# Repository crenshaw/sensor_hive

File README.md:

# Sensor Hive

Another chapter in the Internet of Things.  Sensing the world and pushing data to the cloud.

## About

Buildings are responsible for up to 40% of energy use.  Students and
faculty at the University of Portland are working towards a low-cost
solution for sensing building lighting systems in order to find ways
to provide more efficient lighting.

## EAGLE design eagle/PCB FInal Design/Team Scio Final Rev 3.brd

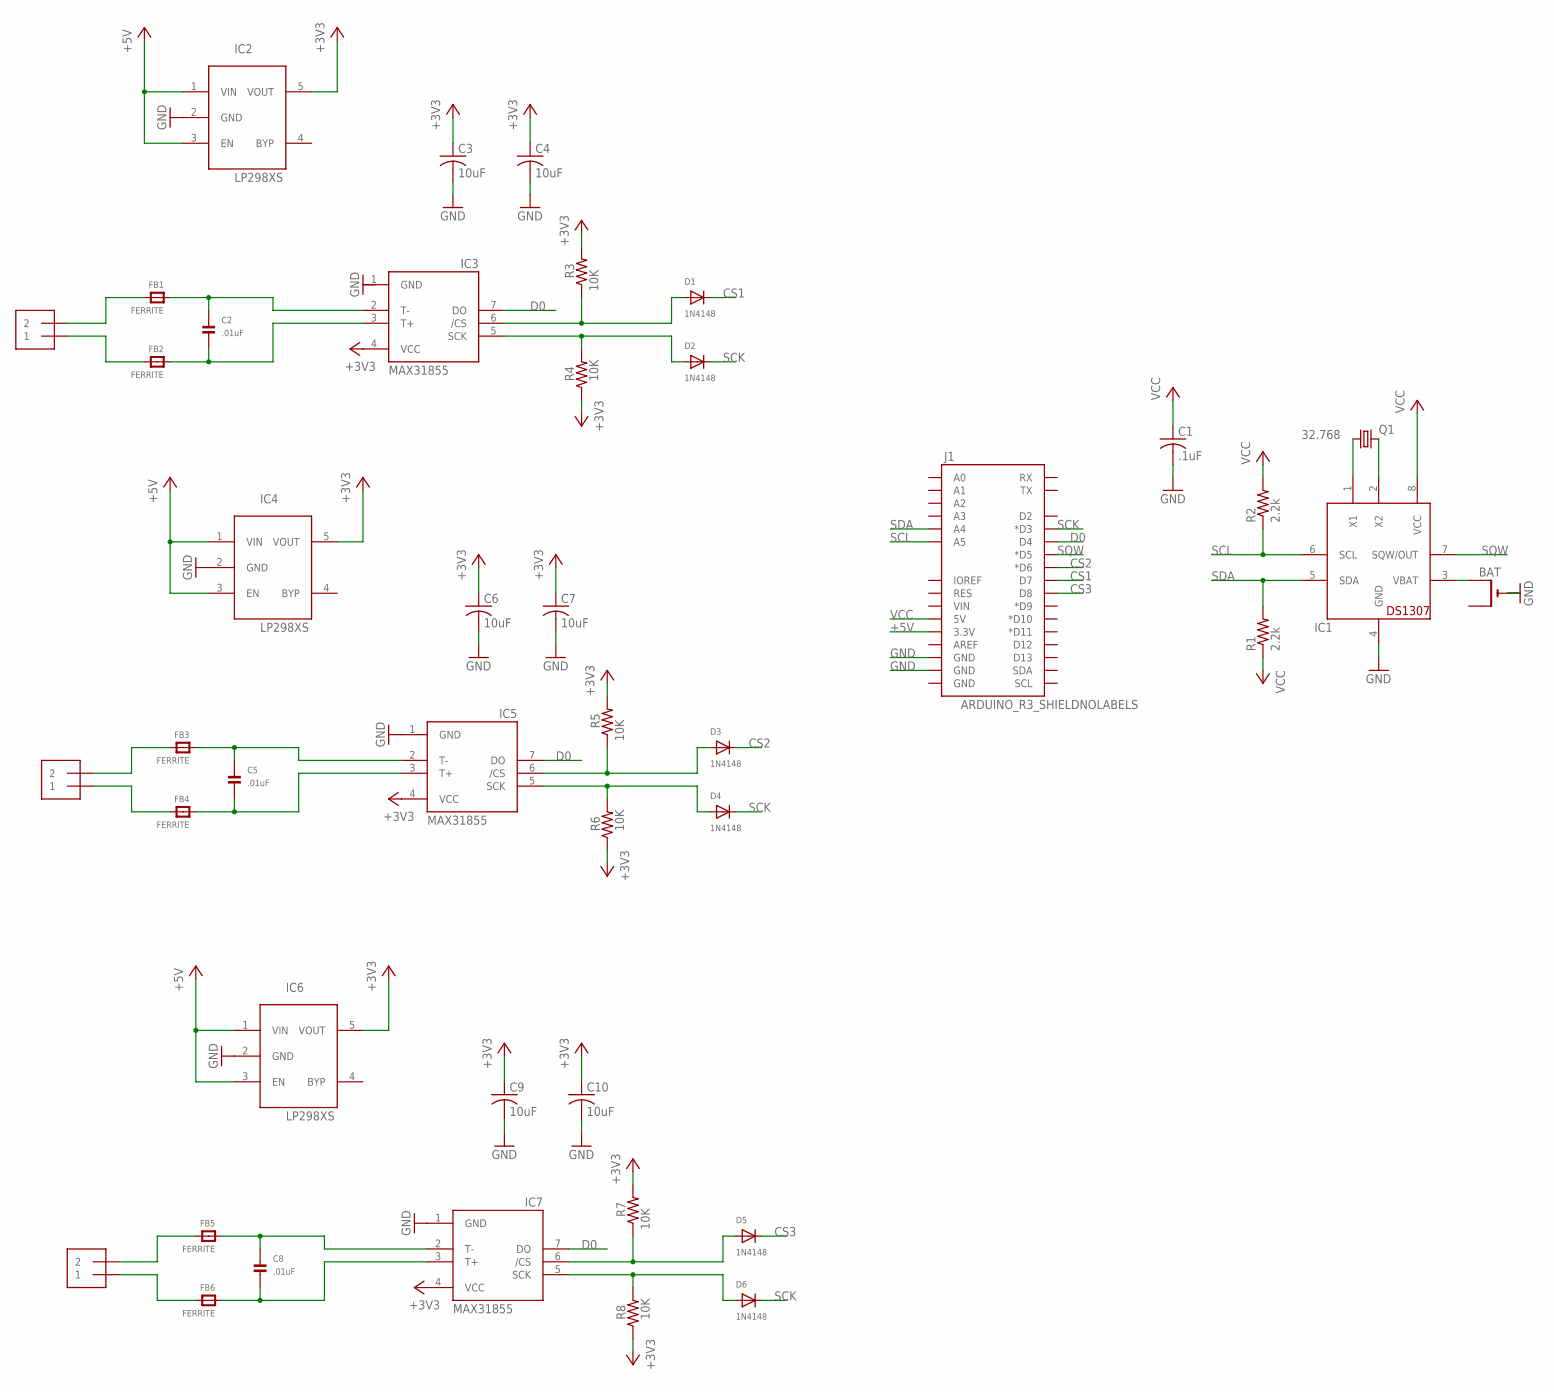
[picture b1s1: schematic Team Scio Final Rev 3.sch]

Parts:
C1: .1uF; C025-025X050
C2, C5, C8: .01uF; 0805
C3, C4, C6, C7, C9, C10: 10uF; C0805K
D1, D2, D3, D4, D5, D6: 1N4148; SOD-323F
FB1, FB2, FB3, FB4, FB5, FB6: FERRITE; 0805
IC1: DS1307; DIL08
IC2, IC4, IC6: LP298XS; SOT23-5L
IC3, IC5, IC7: MAX31855; SO08
J1: ARDUINO_R3_SHIELDNOLABELS; UNO_R3_SHIELD_NOLABELS
J2: J1; 1X2-3.5MM
J3, J4: 1X2-3.5MM
Q1: 32.768; TC38H
R1, R2: 2.2k; M1206
R3, R4, R5, R6, R7, R8: 10K; M1206
RTC: BAT; CR1220-THM

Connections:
+3V3: C3.1, C4.1, C6.1, C7.1, C9.1, C10.1, IC2.5 (VOUT), IC3.4 (VCC), IC4.5 (VOUT), IC5.4 (VCC), IC6.5 (VOUT), IC7.4 (VCC), R3.2, R4.1, R5.2, R6.1, R7.2, R8.1
+5V: IC2.1 (VIN), IC2.3 (EN), IC4.1 (VIN), IC4.3 (EN), IC6.1 (VIN), IC6.3 (EN), J1.3.3V
CS1: D1.C, J1.D7
CS2: D3.C, J1.D6 (*D6)
CS3: D5.C, J1.D8
D0: IC3.7 (DO), IC5.7 (DO), IC7.7 (DO), J1.D4
GND: C1.2, C3.2, C4.2, C6.2, C7.2, C9.2, C10.2, IC1.4 (GND), IC2.2 (GND), IC3.1 (GND), IC4.2 (GND), IC5.1 (GND), IC6.2 (GND), IC7.1 (GND), J1.GND@1 (GND), J1.GND@2 (GND), RTC.-
unnamed: IC1.3 (VBAT), RTC.+2 (+1)
unnamed: IC1.1 (X1), Q1.1
unnamed: IC1.2 (X2), Q1.2
unnamed: FB1.2, J2.2
unnamed: FB2.2, J2.1
unnamed: C2.1, FB1.1, IC3.2 (T-)
unnamed: C2.2, FB2.1, IC3.3 (T+)
unnamed: D1.A, IC3.6 (/CS), R3.1
unnamed: D2.A, IC3.5 (SCK), R4.2
unnamed: FB3.2, J3.2
unnamed: FB4.2, J3.1
unnamed: C5.1, FB3.1, IC5.2 (T-)
unnamed: C5.2, FB4.1, IC5.3 (T+)
unnamed: D3.A, IC5.6 (/CS), R5.1
unnamed: D4.A, IC5.5 (SCK), R6.2
unnamed: FB5.2, J4.2
unnamed: FB6.2, J4.1
unnamed: C8.1, FB5.1, IC7.2 (T-)
unnamed: C8.2, FB6.1, IC7.3 (T+)
unnamed: D5.A, IC7.6 (/CS), R7.1
unnamed: D6.A, IC7.5 (SCK), R8.2
SCK: D2.C, D4.C, D6.C, J1.D3 (*D3)
SCL: IC1.6 (SCL), J1.A5, R2.1
SDA: IC1.5 (SDA), J1.A4, R1.2
SQW: IC1.7 (SQW/OUT), J1.D5 (*D5)
VCC: C1.1, IC1.8 (VCC), J1.5V, R1.1, R2.2

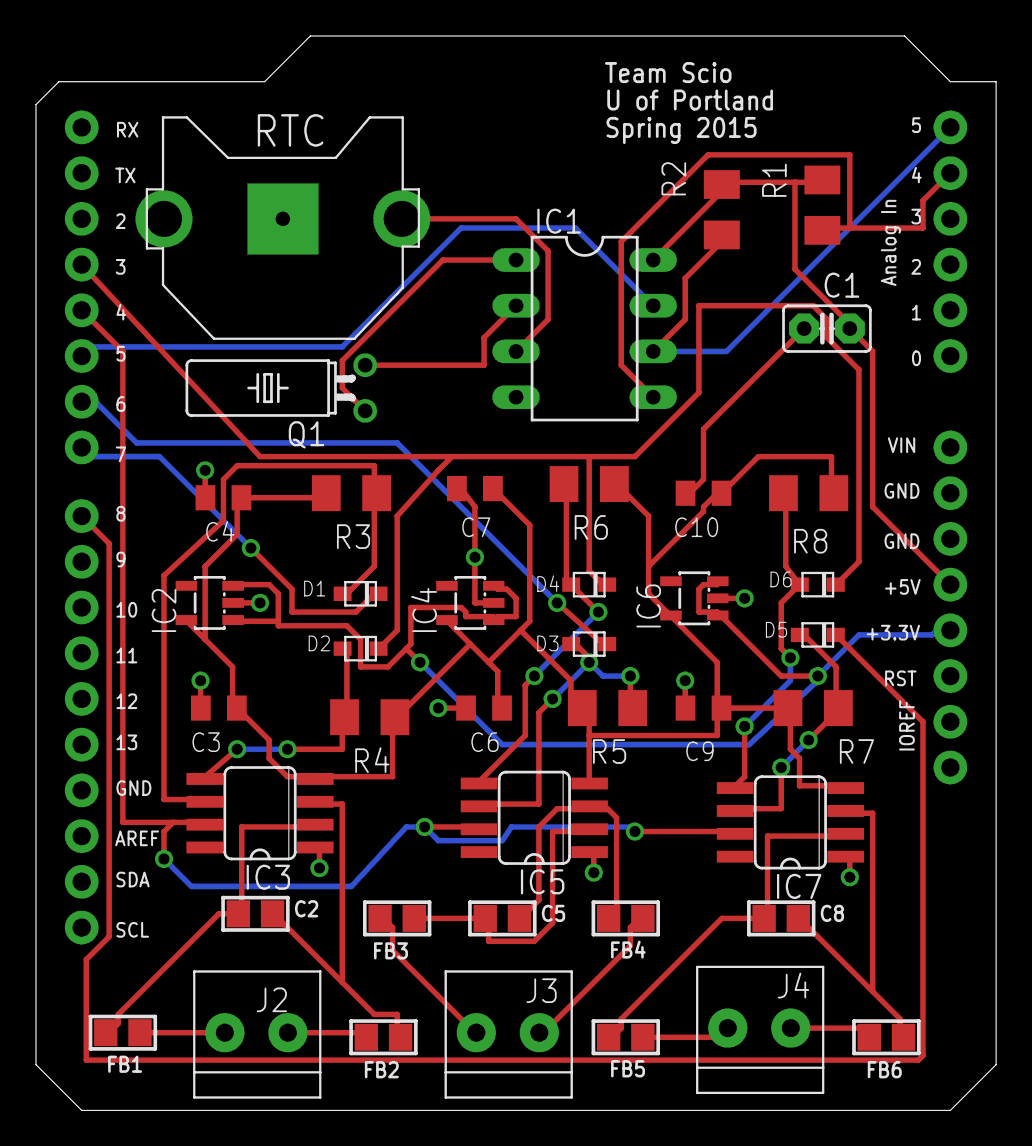
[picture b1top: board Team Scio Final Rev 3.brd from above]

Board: 2 copper layers, 53.3 x 59.7 mm, 43 parts (0 on the bottom side), 33 nets.

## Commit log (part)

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2014-06-05 Initial commit of a Google Packaged App that uses the experimental bluetooth API to list a few properties of a very specific bluetooth device.
2014-06-05 Adding README.md and LICENSE.md files according to GitHub recommendation.
2014-06-18 Adding a working Arduino sketch to measure and report the temperature and humidity captured by the DHT22 sensor. Work largely based on the tutorial provided at https://learn.adafruit.com/bluetooth-te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
2014-06-18 Successfully able to send data to the Arduino and get a well-formed reply of temperature and humidity to the Chrome console over the bluetooth serial connection.
2014-06-20 Data received from the bluetooth serial device is now parsed and logged to the user interface. A 'refresh' button was added to resend requests to the bluetooth serial device.
2014-06-24 User interface now has a reasonably robust 'connect', 'disconnect' and 'refresh' button. User is not allowed to, say, disconnect a device that is already disconnected. A local daq object is now used 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
2014-06-25 Added non-functional buttons for clearing and saving data.
2014-06-28 Initial check-in of Arduino sketches for thermocouple.
2014-07-01 Moving towards getting my box and Arduino to implement the 0R1! command from our miniSD-12 protocol.
2014-07-03 Converting the code so that each daq has its own copy of receive() function and is responsible for receiving unparsed responses for its own connection.
2014-07-03 Made font larger. Using a indicator for when a device is connected. Enforce that only 1 device may be selected at a time by the user. Keeping track of last device selected.
2014-07-07 Accepts commands A, R, and P. Sends data in correct format.
2014-07-08 Midway through implementing 'configure experiment' and 'start experiment' for the user. Getting to this point required some refactoring in terms of how devices were locally registered. Now devices ca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
2014-07-10 Very rudimentary versions of 'configure experiment', 'start experiment', and 'download csv' working. A user can configure an experiment for 2 second period and 10 second duration. The box will issue 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
2014-07-10 Avaliable commands: Continous Measurment #R#!, Set Period 0P#!, and acknowledge Active #!.
2014-07-10 Runs commands a, 0Pn, and, aRn with correctly formatted response.
2014-07-10 Corrected typo in logging experiment information.
2014-07-14 Forgot to save the changes in the Arduino sketch. See previous commit message.
2014-07-14 Tested fixes to miniSDI-12 protocol on Arduino side with user interface. Port number is now being reported correctly by Arduino. Tested fixes to bugs related to starting and configuring an experiment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
2014-07-14 Updating the manifest file with the proper version, 1.0
2014-07-14 Reduced number of buttons in local serial devices menu to be in line with Dr. Dillon's mental model of how the devices and experiments work. Added units back to configure experiment interface, but th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
2014-07-24 Corrected a bug in which clearing the system log or data log prevented all future messages from being logged there.
2014-08-01 The serialApp is now more robustly running R-style experiments. Experiment configuration is logged prettily to the experiment configuration window. It's now possible to run the same experiment over a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
2014-08-04 Added a colon to the last statment sent of D command. Created a daq struct and reimplemented main program. Moved R cmds to function in implementation file.
2014-08-04 Corrected a small typo in how disabled devices were being reported to the user interface.
2014-08-04 Corrected a small bug in which the App thought the experiment was complete before it was actually completed.
2014-08-04 Commands A, P, R, M, and D work from the master end. Added comments to read_write.cpp. Uploading latest working version before I try and implement writing to non-volitile memory which may break every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
2014-08-06 Added a serial console so that I could watch all the raw serial communication between the application and the DAQ. Cleaned up all console.log() messages; now there are none of those. Affirmed that I 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
2014-08-08 Able to clear experiment settings. When an experiment is cleared, all devices associated with the experiment are also cleared.
2014-08-08 Preparing to merge with develop branch. Updated version of application to 1.1.
2014-08-11 Runes Commands A, P, R, M, and D. Stores data to EEPROM and runs recovery algorithm on startup. Will continue an experiment on startup if the Arduino was reset or lost power while an experiment was r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
2014-08-11 Application is now fairly robust against losing a device during an R-style experiment (desktop only logging). An onReceiveError() function is invoked when a connection is lost. This function marks a 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
2014-08-13 A first draft of a working application in which the application loses a connection with a DAQ and then reestablishes the connection during an experiment with daq-style logging.
2014-08-14 Added a stop button that makes use of the underlying mini-SDI12 break command to stop M-style experiments. Button is working and behaving as expected.
2014-08-15 Removed the Serial Log to prepare for the user studies to come in the next couple of days. User studies will take place from the serialApp branch.
2014-08-16 Fixed a bug so that the daq qill repsond with the abort response if prompted with a D command before data is ready to be sent.
2014-08-25 Removed three debug statments that were left in by mistake.
2014-09-01 Parsed the datum string and inserted it into a table with headers. This is not ready to be pushed to production code. There are todos to be resolved after learning more about the codebase in first me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
2014-09-07 Commands A R M P and D work. Added functionality to the D command such that aDm retrieves the last m meansurments that were taken from port a. The EEPROM now holds up to the most recent 144 measurmen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
2014-09-19 Checking this in for the night. This is really incomplete, I would recommend not looking at this until a future push. Currently have the indexedDB working, but extra functionality may be needed. Next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
2014-09-21 Upadted the aDn command so that it returns correct number of measuremetns. see issue number 5 for a complete description.
2014-09-23 Removed strange characters from comments in EEPROMex.h. Arduino IDE was complaining about characters that were not UTF-8 encoded, and removing these characters corrected the complaining.
2014-09-29 Continued to work on locally backing up data. Modified the UI so that there is now an experiments list in the data window. Next steps are to test it out with a real DAQ. Some more UI changes will be 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
2014-09-29 Added more icons to icons.ai for future poster.
2014-10-06 Added basic GET endpoint to retrieve all experiment data from the db.
2014-10-06 Add GET endpoint for single experiment's data
2014-10-07 Got the multiexperiment data window working. It seems to be working well. Basic functionality works. Experiment data is stored locally to an indexed database. More rigorous testing should occur. The 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
2014-10-07 Adding icons for 'authenticate' and 'push' operations.
2014-10-11 Resolving issue #13. Application font is larger; window does not exceed height 800, and serial port log is now selectable.
2014-10-11 Added parens around the S and the D in the experiments list because the SD were dangerously close together and it felt like somebody could inadvertedly delete a 4-day experiment. There's definitely a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
2014-10-19 Removed a debug statment, and added an implementation of breakRoutine
2014-10-19 removed old code
2014-10-19 The new verison of the DAQ code. Allows for multiple sensor types. Should fully implement all commands sent via miniSDI_12 protocol.
2014-10-21 In reference to issue #19 and issue #15, these are both closed in this commit. The formatting is fixed for daq/desktop experiments and the data window stays scrolled to the bottom.
2014-10-27 Initial Data Viewing
2014-10-27 Data is now being uploaded to the cloud server.
2014-11-02 I added an upload button to address #22 that pushes an experiment to the cloud in case of areas with no internet. I also added a checkbox in experiment configuration to enable or disable storing info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
2014-11-02 Fixed a bug with the setting of the Timer/Counter 1 external clock pin. This is pin 5 on the arduino and needs to be set as INPUT_PULLUP. Previously was not set.
2014-11-03 added mockups for design document
2014-11-03 initial data visualization in place
2014-11-06 Data Visualization v.1
2014-11-07 Fixed an incorrect constant. MEMORY_SIZE was defined as 1048. This should be and now is 1024.
2014-11-08 Adding some server-specific information to my .gitignore list.
2014-11-08 Adding a variety of logging messages to help me figure out what happened just before an application crash.
2014-11-20 Fixed the incorrect dates due to me forgetting that Javascript doesn't zero index the dates consistently.
2015-01-26 WIP: Adding secured route to add user to DB
2015-01-28 Add user functionality
    Added route and DatabaseManager function to add a user to the DB. Changed schema
    to fit new understanding of bcrypt.
2015-01-28 Added CSV download support functionality.
    Not Complete yet but it works.
2015-02-09 Added auth route to backend and WIP on frontend
2015-02-11 Add loading spinner and modify server response on bad request
2015-02-18 Remove error logging, small frontend loading bug fix
2015-02-25 Client side hashing in place
2015-03-04 Added login area to local app
2015-03-23 Change timestamp to use the value provided by the DAQ, rather than a value generated from javascript. To address #38
2015-03-30 Added relevant files
2015-04-03 Updated and added function headers and comments
2015-04-06 Fix merge issues
2015-04-17 Added comments and function headers.
2015-07-14 Changed header for System log
2015-07-16 Adding basic comment header to cloud.js.
2015-07-20 Adding subtract and configure icons to ~/box/public/icons/. Icons are available as 32x32 pt .png files and are also available in the illustrator ai file in ~/art.
2015-07-21 Added new buttons and made all buttons small. Reformatted Configure section.
2015-07-27 Adding the lost file daq.ino to this branch. My eventual goal is to add it to the develop branch in full working order.
2015-07-29 Added functionality for lock/unlock button. Saves configuration and enables/disables checkbox as needed.
2015-07-29 Updating spelling of behaviour in main.js
2015-07-29 test commit, made sooo many changes to all the files.
2015-08-03 Corrected a small bug in bt.devices.getRegistry() so that devices that are not in the current app registry are reported. Added another debugging function, bt.devices.getState() as I try to refine pre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
2015-08-04 Fixed Registered Devices List bug.
2015-08-04 Reformatted data menu.
2015-08-05 Fixed formatting of data table titles.
2015-08-11 Login box moved to correct position, added disappearing function when logged in. Temp Scio logo added to banner with link to remote viewer page.
2015-08-14 Login/logout works and the spans are back. yay
2015-08-14 Placing lightbulb-clear.png in the correct directory.
2015-08-18 Spans for configure now show completely.
2015-08-19 Fixed span on download and upload buttons in data menu. Added errors when experiment to download/upload not selected. Fixed clearing of serial port log window.
2015-09-01 Server changes to be able to push changes directly to server. style.css currently not working.
2015-09-06 File changed to accept CSS file type.
2015-09-11 Adding larger sized clear lightbulb image.
2015-11-10 Changed styling of remote view. Changed color and appearance. Added files for selectize to be implemented for experiment selection.
2015-12-04 Test commit.
2015-12-04 Adding image files and style files not previously added correctly.
2015-12-04 Merging with working server version after deleting unnecessary files.

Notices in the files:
parts and their libraries:
SparkFun-Boards: Licensing: Creative Commons ShareAlike 4.0 International - https://creativecommons.org/licenses/by-sa/4.0
microbuilder: This work is placed in the public domain, and may be freely used for commercial and non-commercial work with the following conditions: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
